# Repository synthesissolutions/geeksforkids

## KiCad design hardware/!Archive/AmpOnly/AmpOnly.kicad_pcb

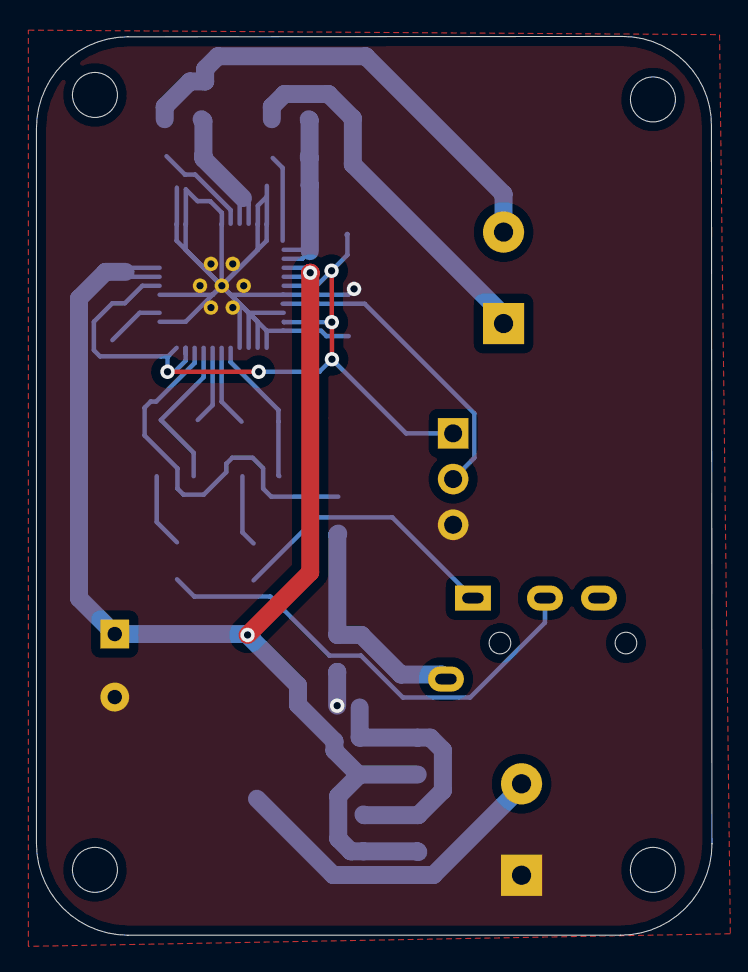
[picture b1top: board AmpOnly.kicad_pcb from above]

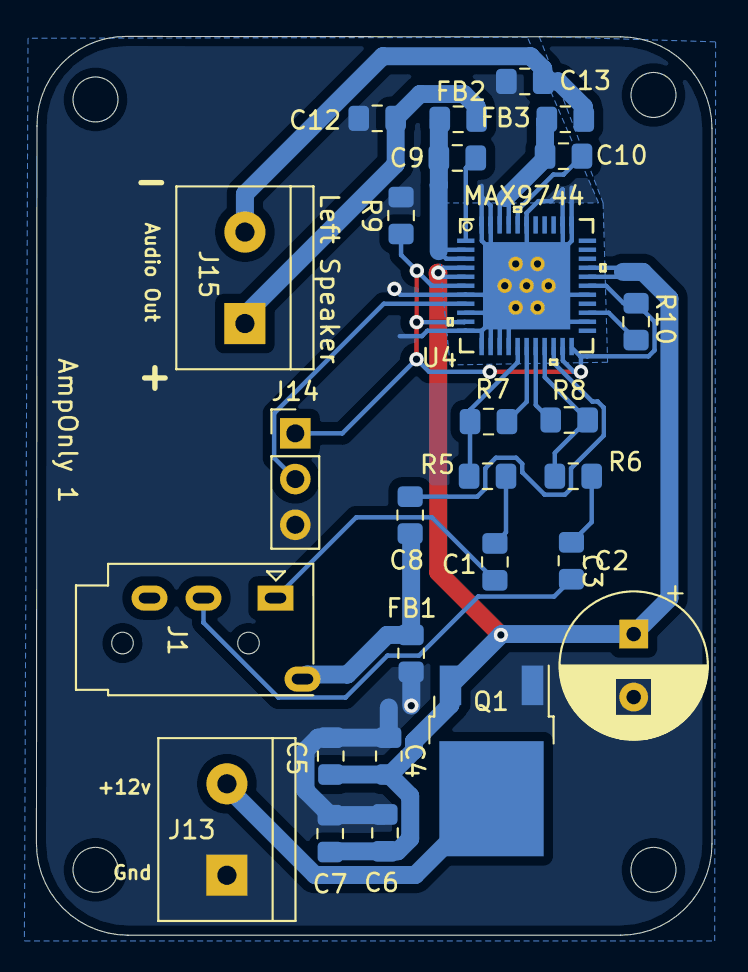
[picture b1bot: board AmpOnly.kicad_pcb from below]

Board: 2 copper layers, 37.5 x 49.9 mm, 27 parts (27 on the bottom side), 22 nets.

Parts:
C1, C2: 0.47µF; C_0805_2012Metric_Pad1.15x1.40mm_HandSolder
C3: 470µF; CP_Radial_D8.0mm_P3.50mm
C4, C5: 10µF; C_0805_2012Metric_Pad1.15x1.40mm_HandSolder
C6, C7, C9, C10: 0.1µF; C_0805_2012Metric_Pad1.15x1.40mm_HandSolder
C8: 2.2µF; C_0805_2012Metric_Pad1.15x1.40mm_HandSolder
C12, C13: 470pF; C_0805_2012Metric_Pad1.15x1.40mm_HandSolder
FB1, FB2, FB3: MPZ2012S221AT00; L_0805_2012Metric_Pad1.15x1.40mm_HandSolder
J1: AudioJack4; Jack_3.5mm_PJ320A_Horizontal_Short
J13: Main Power; TerminalBlock_bornier-2_P5.08mm
J14: Volume; PinHeader_1x03_P2.54mm_Vertical
J15: Left Speaker; TerminalBlock_bornier-2_P5.08mm
Q1: AOD417; TO-252-2pin3D
R5, R6, R7, R8: 20K; R_0805_2012Metric_Pad1.15x1.40mm_HandSolder
R9, R10: 10K; R_0805_2012Metric_Pad1.15x1.40mm_HandSolder
U4: MAX9744; max9744eth&plus_Mod

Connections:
+3V3: J14.1, R9.1, R10.2, U4.6, U4.10, U4.21, U4.22, U4.28
+12V: J13.2, Q1.3
GND: C3.2, C4.1, C5.1, C6.1, C7.1, C12.1, C13.2, FB1.2, J13.1, J14.3, Q1.1, R9.2, U4.7, U4.9, U4.11, U4.12, U4.13, U4.14, U4.15, U4.24, U4.27, U4.34, U4.35, U4.39, U4.43, U4.44, U4.45
GNDA: C8.2, FB1.1, J1.S
LeftIN: C1.2, J1.T
unnamed: C1.1, R5.2
unnamed: C2.1, R6.2
unnamed: C3.1, C4.2, C5.2, C6.2, C7.2, Q1.2, U4.4, U4.5, U4.29, U4.30
unnamed: C8.1, U4.20
unnamed: C9.1, FB2.1, U4.2, U4.3
unnamed: C9.2, U4.1
unnamed: C10.1, FB3.1, U4.41, U4.42
unnamed: C10.2, U4.40
unnamed: C12.2, FB2.2, J15.1
unnamed: C13.1, FB3.2, J15.2
unnamed: J14.2, U4.8
unnamed: R5.1, R7.2, U4.16
unnamed: R6.1, R8.2, U4.19
unnamed: R7.1, U4.17
unnamed: R8.1, U4.18
unnamed: R10.1, U4.25
RightIN: C2.2, J1.R1

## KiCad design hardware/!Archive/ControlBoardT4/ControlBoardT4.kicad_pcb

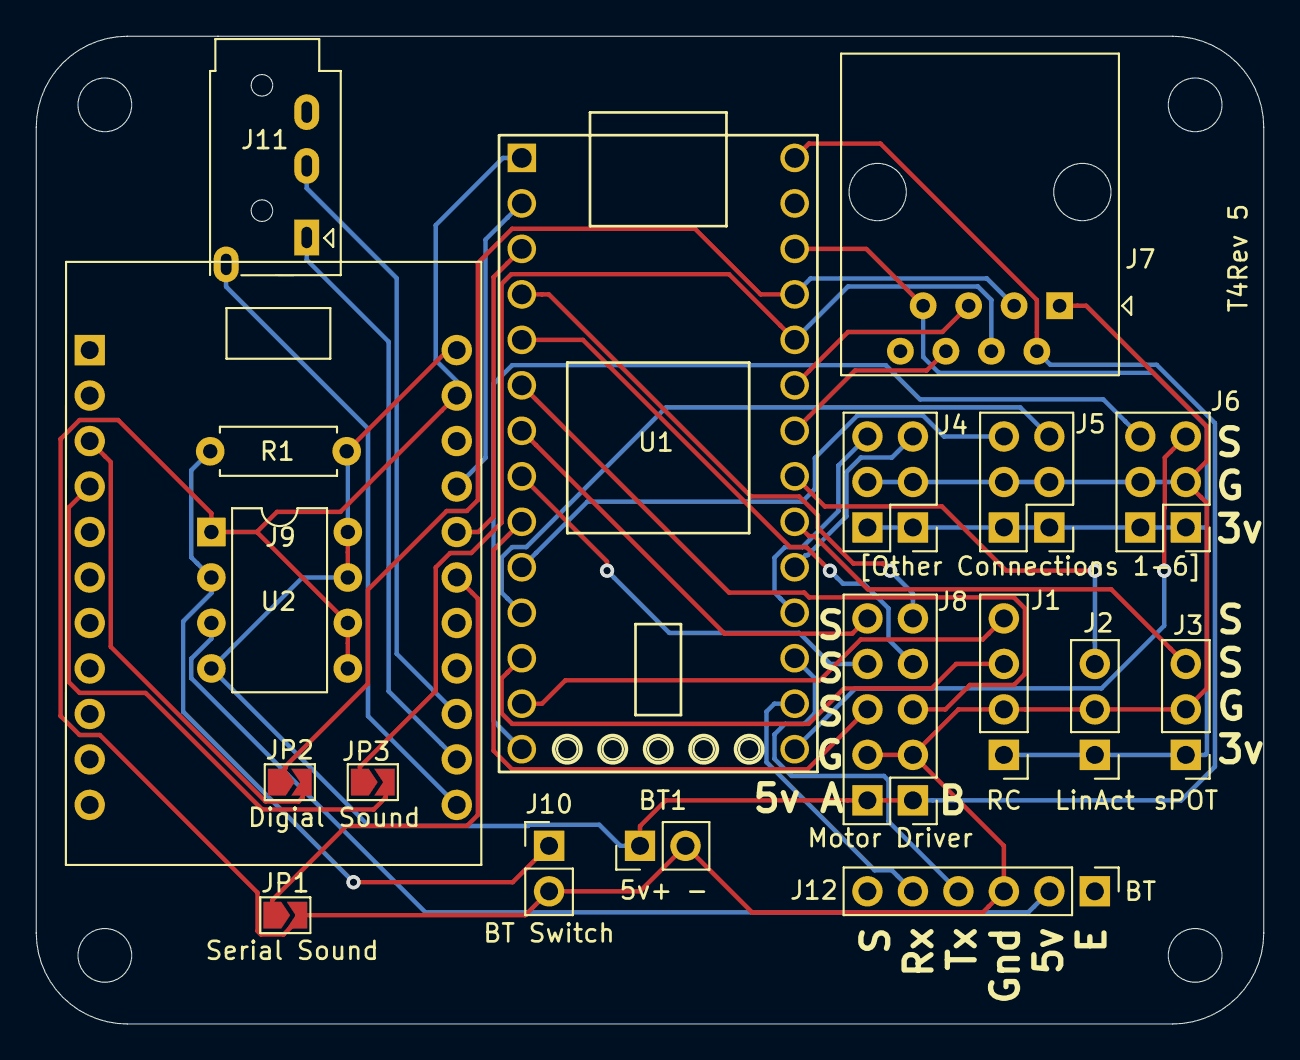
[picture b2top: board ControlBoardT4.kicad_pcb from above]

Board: 2 copper layers, 68.6 x 55.2 mm, 19 parts (0 on the bottom side), 35 nets.

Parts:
BT1: 5v+ -; PinHeader_1x02_P2.54mm_Vertical
J1: RC; PinHeader_1x04_P2.54mm_Vertical
J2: LinAct; PinHeader_1x03_P2.54mm_Vertical
J3: sPOT; PinHeader_1x03_P2.54mm_Vertical
J4: Other 1 & 2; PinHeader_2x03_P2.54mm_Vertical
J5: [Other Connections 1-6]; PinHeader_2x03_P2.54mm_Vertical
J6: Other 5 & 6; PinHeader_2x03_P2.54mm_Vertical
J7: 8P8C; RJ45_Amphenol_54602-x08_Horizontal
J8: Motor Driver; PinHeader_2x05_P2.54mm_Vertical
J9: FXSound; FXSound_2x11_P2.54mm
J10: BT Switch; PinHeader_1x02_P2.54mm_Vertical
J11: AudioJack4; Jack_3.5mm_PJ320A_Horizontal
J12: BT; PinHeader_1x06_P2.54mm_Vertical
JP1: Serial Sound; SolderJumper-2_P1.3mm_Open_TrianglePad1.0x1.5mm
JP2, JP3: Digial Sound; SolderJumper-2_P1.3mm_Open_TrianglePad1.0x1.5mm
R1: R; R_Axial_DIN0207_L6.3mm_D2.5mm_P7.62mm_Horizontal
U1: Teensy4.0_NoMid; Teensy40_NoMid
U2: NA555; DIP-8_W7.62mm

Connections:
+3V3: J1.1, J2.1, J3.1, J4.1, J4.2, J5.1, J5.2, J6.1, J6.2, J7.7, U1.26
+5V: BT1.1, J7.2, J8.1, J8.2, J9.2, R1.2, U1.28, U2.4, U2.7, U2.8
GND: BT1.2, J1.2, J2.2, J3.2, J4.3, J4.4, J5.3, J5.4, J6.3, J6.4, J7.1, J8.3, J8.4, J9.4, J10.2, J12.3, JP1.2, U1.1, U2.1, U2.5, U2.6
unnamed: J1.3, U1.12
unnamed: J1.4, U1.13
unnamed: J2.3, U1.21
unnamed: J3.3, U1.20
unnamed: J4.5, U1.19
unnamed: J4.6, U1.18
unnamed: J5.5, U1.11
unnamed: J5.6, U1.10
unnamed: J6.5, U1.15
unnamed: J6.6, U1.14
unnamed: J7.3, JP2.1, U1.25
unnamed: J7.4, JP3.1, U1.24
unnamed: J7.5, U1.23
unnamed: J7.6, U1.22
unnamed: J8.5, U1.6
unnamed: J8.6, U1.9
unnamed: J8.7, U1.5
unnamed: J8.8, U1.8
unnamed: J8.9, U1.4
unnamed: J8.10, U1.7
unnamed: J9.5, JP2.2
unnamed: J9.7, JP3.2
unnamed: J9.8, U1.2
unnamed: J9.10, U1.3
unnamed: J9.12, JP1.1
unnamed: J10.1, R1.1, U2.2
unnamed: J9.18, J11.R1
unnamed: J9.22, J11.S
unnamed: J9.20, J11.T
unnamed: J12.2, U2.3
unnamed: J12.4, U1.17
unnamed: J12.5, U1.16

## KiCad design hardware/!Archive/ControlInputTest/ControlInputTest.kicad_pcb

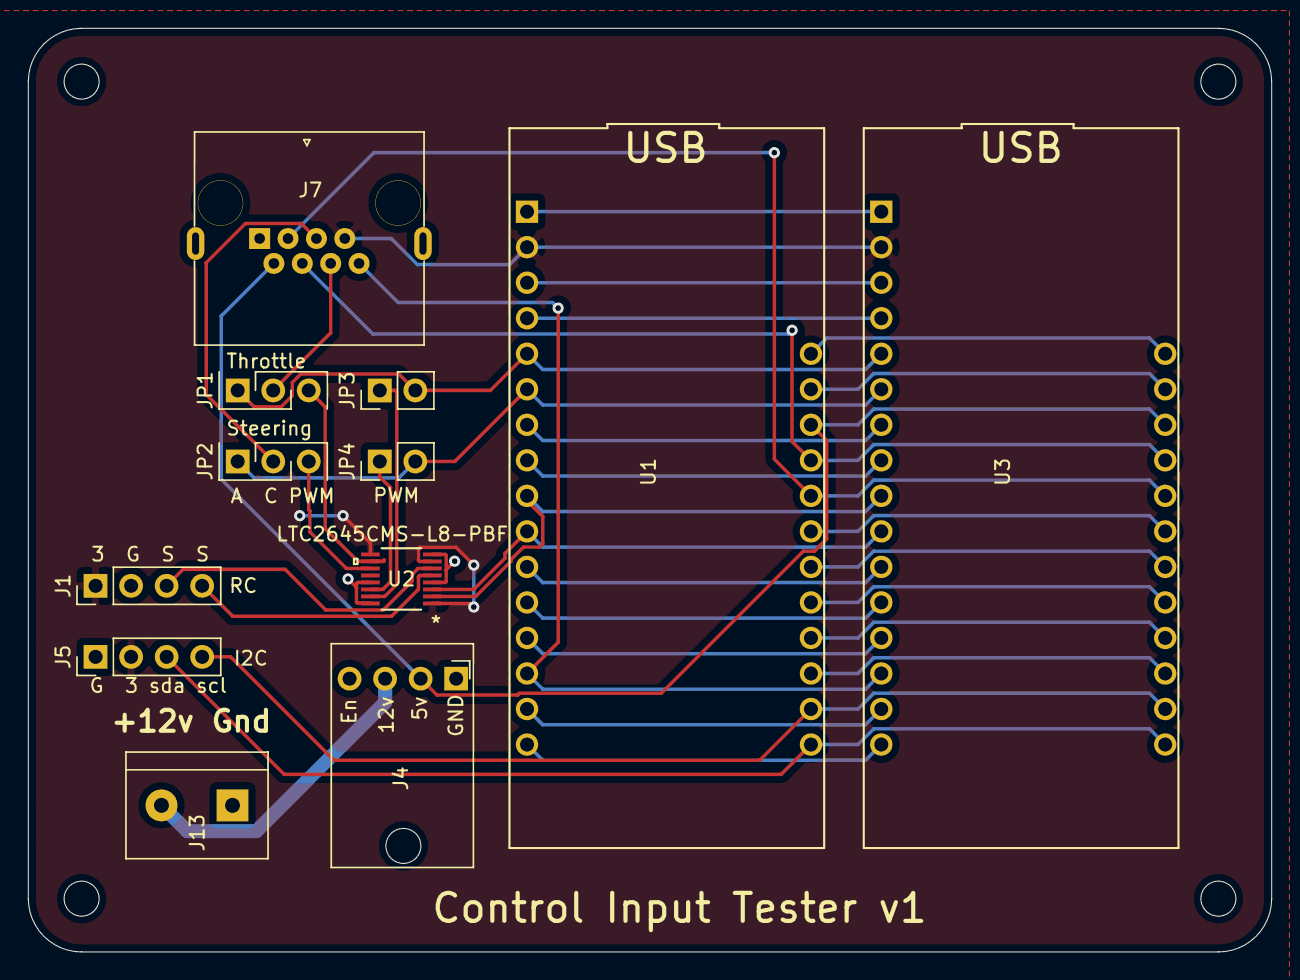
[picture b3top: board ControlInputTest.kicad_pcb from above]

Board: 2 copper layers, 88.9 x 66.0 mm, 12 parts (0 on the bottom side), 37 nets.

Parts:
J1: RC; PinHeader_1x04_P2.54mm_Vertical
J4: Power Input; AdaFruit_MPM3610
J5: I2C; PinHeader_1x04_P2.54mm_Vertical
J7: 8P8C; RJ45_x08_Tab_Up
J13: Main Power; TerminalBlock_bornier-2_P5.08mm
JP1: Throttle Jumper; PinHeader_1x03_P2.54mm_Vertical
JP2: Steering Jumper; PinHeader_1x03_P2.54mm_Vertical
JP3: LTC Throttle Jumper; PinHeader_1x02_P2.54mm_Vertical
JP4: LTC Steering Jumper; PinHeader_1x02_P2.54mm_Vertical
U1, U3: Feather_nRF52840
U2: LTC2645CMS-L8-PBF

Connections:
+3V3: J1.1, J5.2, J7.7, U1.2, U2.1, U2.7, U2.9, U3.2
+5V: J4.2, J7.2, U1.26, U3.26
+12V: J4.3, J13.2
A2: U1.7, U3.7
A3: U1.8, U3.8
AREF: U1.3, U3.3
ActiveSW: J7.8, U1.14, U3.14
BAT: U1.28, U3.28
D2: U1.16, U3.16
D5: U1.19, U3.19
D6: U1.20, U3.20
D9: U1.21, U3.21
D10: U1.22, U3.22
D11: U1.23, U3.23
D12: J7.3, U1.24, U3.24
D13: J7.4, U1.25, U3.25
EN: U1.27, U3.27
GND: J1.2, J4.1, J5.1, J7.1, J13.1, U1.4, U2.4, U2.8, U2.13, U2.16, U3.4
I2C_SCL: J5.4, U1.18, U3.18
I2C_SDA: J5.3, U1.17, U3.17
MI: U1.13, U3.13
MO: U1.12, U3.12
unnamed: J7.5, JP2.2
unnamed: J7.6, JP1.2
unnamed: JP3.1, U2.15
unnamed: JP4.1, U2.14
PWMSteering: JP2.3, U2.11
PWMThrottle: JP1.3, U2.10
RCAnalogSteering: U1.10, U2.3, U3.10
RCAnalogThrottle: U1.9, U2.2, U3.9
RCPWMSteering: J1.4, U2.5
RCPWMThrottle: J1.3, U2.6
RST: U1.1, U3.1
SCK: U1.11, U3.11
Steering: JP2.1, JP4.2, U1.6, U3.6
TX: U1.15, U3.15
Throttle: JP1.1, JP3.2, U1.5, U3.5

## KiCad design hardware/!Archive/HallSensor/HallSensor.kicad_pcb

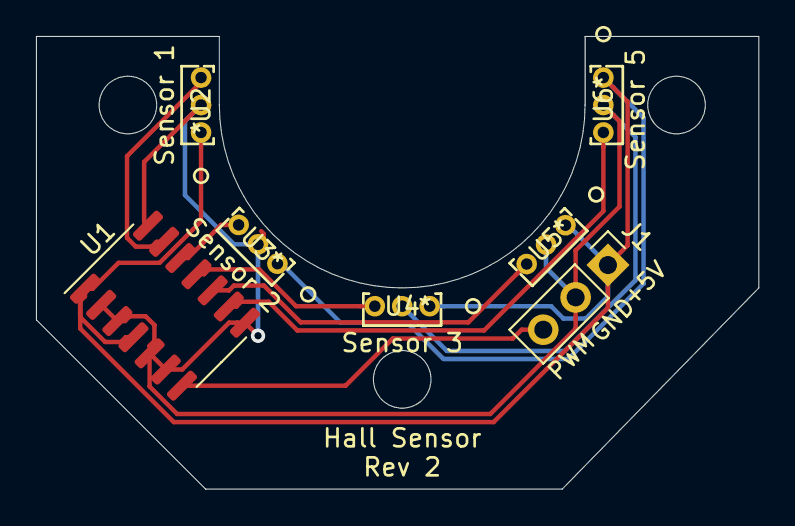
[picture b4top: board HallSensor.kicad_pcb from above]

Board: 2 copper layers, 40.1 x 25.1 mm, 7 parts (0 on the bottom side), 8 nets.

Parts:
J1: Power_Signal; PinHeader_1x03_P2.54mm_Vertical
U1: ATtiny841-SSU; SOIC-14_3.9x8.7mm_P1.27mm
U2: Sensor 1; SS49E
U3: Sensor 2; SS49E
U4: Sensor 3; SS49E
U5: SS49E
U6: Sensor 5; SS49E

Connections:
+5V: J1.1, U1.1, U1.4, U2.1, U3.1, U4.1, U5.1, U6.1
GND: J1.2, U1.2, U1.3, U1.5, U1.6, U1.8, U1.14, U2.2, U3.2, U4.2, U5.2, U6.2
unnamed: J1.3, U1.7
unnamed: U1.9, U6.3
unnamed: U1.10, U5.3
unnamed: U1.11, U4.3
unnamed: U1.12, U3.3
unnamed: U1.13, U2.3

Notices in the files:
parts and their libraries:
Copyright 2016 Accelerated Designs. All rights reserved.
